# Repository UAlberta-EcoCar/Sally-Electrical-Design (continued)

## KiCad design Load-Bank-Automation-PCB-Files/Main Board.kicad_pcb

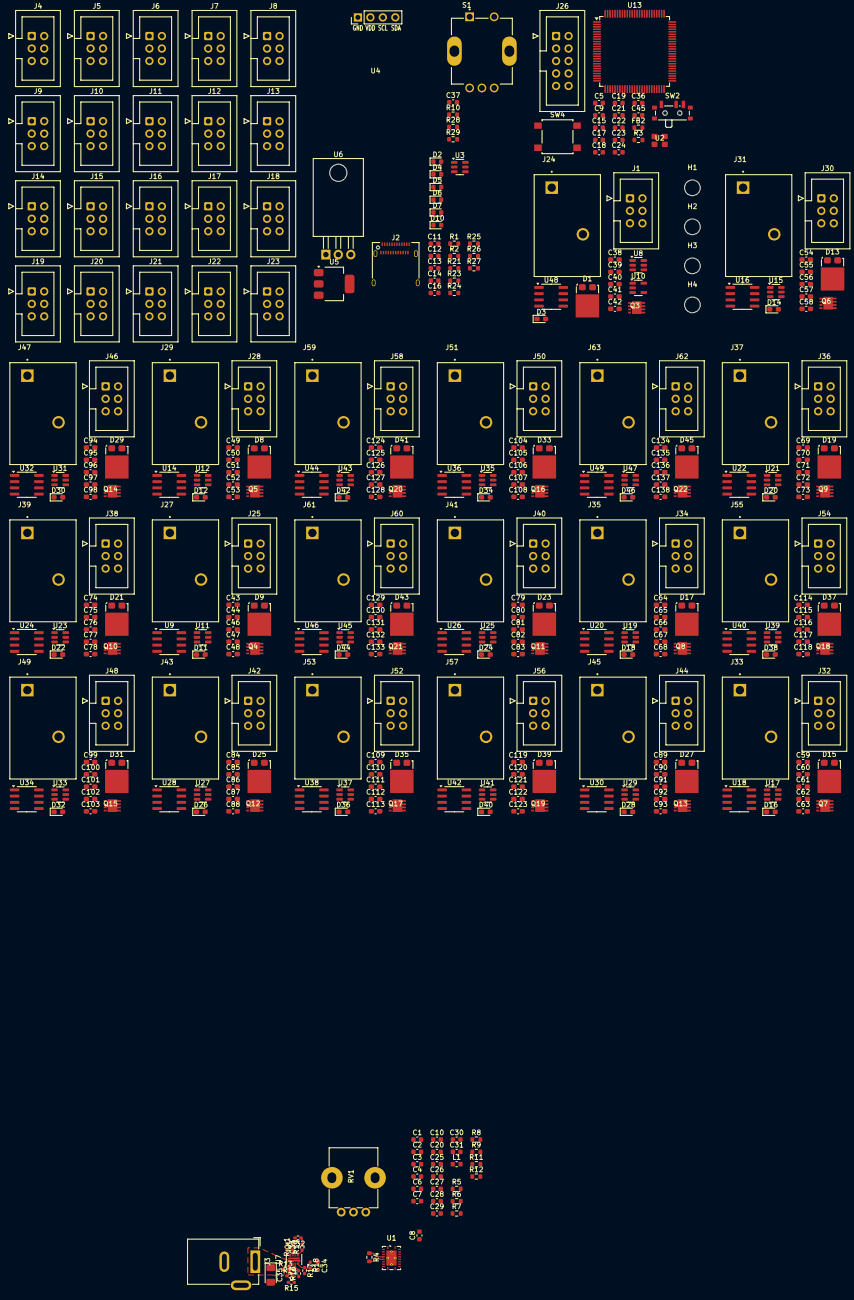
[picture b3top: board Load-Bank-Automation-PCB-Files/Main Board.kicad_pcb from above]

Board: 2 copper layers, 354 parts (0 on the bottom side), 237 nets.

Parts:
C1: 2200n; C_0603_1608Metric
C2: 82p; C_0603_1608Metric
C3, C5, C9, C12, C13, C14, C17, C18, C19, C21, C31, C36, C37, C45: 100n; C_0603_1608Metric
C4: 47n; C_0603_1608Metric
C6, C16, C20, C25, C26: 10u; C_0603_1608Metric
C7, C27, C28, C29: 22u; C_0603_1608Metric
C8: 5.6n; C_0603_1608Metric
C10: 820p; C_0603_1608Metric
C11: 330n; C_0603_1608Metric
C15: 4u7; C_0603_1608Metric
C22: 10n; C_0603_1608Metric
C23, C24: 1u; C_0603_1608Metric
C30: 12p; C_0603_1608Metric
C32: 2200p; R_0402_1005Metric_Pad0.72x0.64mm_HandSolder
C33: C; R_0402_1005Metric_Pad0.72x0.64mm_HandSolder
C34: 240u; R_0603_1608Metric
C35: 100u; D_1206_3216Metric_Pad1.42x1.75mm_HandSolder
C38, C39, C43, C44, C49, C50, C54, C55, C59, C60, C64, C65, C69, C70, C74, C75, C79, C80, C84, C85, C89, C90, C94, C95, C99, C100, C104, C105, C109, C110, C114, C115, C119, C120, C124, C125, C129, C130, C134, C135: 100u; C_0603_1608Metric_Pad1.08x0.95mm_HandSolder
C40, C41, C46, C47, C51, C52, C56, C57, C61, C62, C66, C67, C71, C72, C76, C77, C81, C82, C86, C87, C91, C92, C96, C97, C101, C102, C106, C107, C111, C112, C116, C117, C121, C122, C126, C127, C131, C132, C136, C137: C; C_0603_1608Metric_Pad1.08x0.95mm_HandSolder
C42, C48, C53, C58, C63, C68, C73, C78, C83, C88, C93, C98, C103, C108, C113, C118, C123, C128, C133, C138: 0.1u; C_0603_1608Metric_Pad1.08x0.95mm_HandSolder
D1, D8, D9, D13, D15, D17, D19, D21, D23, D25, D27, D29, D31, D33, D35, D37, D39, D41, D43, D45: STPS5H100SFY; TO-277A
D2, D4, D5, D6, D7, D10: LED; LED_0603_1608Metric
D3, D11, D12, D14, D16, D18, D20, D22, D24, D26, D28, D30, D32, D34, D36, D38, D40, D42, D44, D46: LED; LED_0603_1608Metric_Pad1.05x0.95mm_HandSolder
FB2: 300R; R_0603_1608Metric
H1, H2, H3, H4: MountingHole; MountingHole_3.2mm_M3
J1, J4, J5, J6, J7, J8, J9, J10, J11, J12, J13, J14, J15, J16, J17, J18, J19, J20, J21, J22, J23, J25, J28, J30, J32, J34, J36, J38, J40, J42, J44, J46, J48, J50, J52, J54, J56, J58, J60, J62: Conn_02x03_Counter_Clockwise; IDC-Header_2x03_P2.54mm_Vertical
J2: USB_C_Receptacle_USB2.0_14P; USB_C_Receptacle_Amphenol_12401610E4-2A
J3: Barrel_Jack_MountingPin; BarrelJack_GCT_DCJ200-10-A_Horizontal
J24, J27, J29, J31, J33, J35, J37, J39, J41, J43, J45, J47, J49, J51, J53, J55, J57, J59, J61, J63: PHNX_CONN_1017521; PHOENIX_1017521
J26: STM32-Prog-Header; IDC-STM32-Prog-Header_2x05_P2.54mm_Vertical
L1: 5600n; L_0603_1608Metric
Q3, Q4, Q5, Q6, Q7, Q8, Q9, Q10, Q11, Q12, Q13, Q14, Q15, Q16, Q17, Q18, Q19, Q20, Q21, Q22: GSGN0648; Goodarksemiconductor_PPAK_3x3
R1, R2: 5k1; R_0603_1608Metric
R3: 10K; R_0603_1608Metric
R4: 1.5k; R_0603_1608Metric
R5: 10k; R_0603_1608Metric
R6: 500; R_0603_1608Metric
R7: 21k; R_0603_1608Metric
R8: 23.7k; R_0603_1608Metric
R9: 100; R_0603_1608Metric
R10: 5K; R_0603_1608Metric
R11: 80k6; R_0603_1608Metric
R12, R23, R24, R27: 7k5; R_0603_1608Metric
R13: 470k; R_0402_1005Metric_Pad0.72x0.64mm_HandSolder
R14: 16k; R_0402_1005Metric_Pad0.72x0.64mm_HandSolder
R15: 25k; R_0402_1005Metric_Pad0.72x0.64mm_HandSolder
R16, R18: 47K; R_0402_1005Metric_Pad0.72x0.64mm_HandSolder
R17: 3k9; R_0402_1005Metric_Pad0.72x0.64mm_HandSolder
R19: 100; R_0402_1005Metric_Pad0.72x0.64mm_HandSolder
R21: 2k; R_0603_1608Metric
R25, R26: 600; R_0603_1608Metric
R28, R29: 4k7; R_0603_1608Metric
RV1: 10K; Potentiometer_Bourns_PTV09A-4_Single_Vertical
R_{ILM}1: 750; R_0402_1005Metric_Pad0.72x0.64mm_HandSolder
S1: PEC12R-4220F-S0024; XDCR_PEC12R-4220F-S0024
SW2: SW_SPDT; SW_SPDT_PCM12
SW4: RESET; SW_SPST_B3S-1000
U1: LM25145RGYT; Texas_RGY_R-PVQFN-N20_EP2.05x3.05mm_ThermalVias
U2: OXETDLJANF-8MHz
U3: USBLC6-2SC6; SOT-23-6
U4: 1306 OLED Display; Display_128x64_096_I2C
U5: LD1117S33TR_SOT223; SOT-223-3_TabPin2
U6: L7805; TO-220-3_Horizontal_TabDown
U7: TPS259474LRPWR; RPW0010A-MFG
U8, U11, U12, U15, U17, U19, U21, U23, U25, U27, U29, U31, U33, U35, U37, U39, U41, U43, U45, U47: IRS10752LPBF; SOT-23-6
U9, U14, U16, U18, U20, U22, U24, U26, U28, U30, U32, U34, U36, U38, U40, U42, U44, U46, U48, U49: ACS711xLCTR-25AB; SOIC-8_3.9x4.9mm_P1.27mm
U10: MCP6006-OTVAO; SOT-23-5
U13: STM32G491VETx; LQFP-100_14x14mm_P0.5mm

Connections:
+3V3: C5.1, C9.1, C15.1, C16.1, C17.1, C18.1, C19.1, C21.1, C24.1, C36.1, C42.2, C48.2, C53.2, C58.2, C63.2, C68.2, C73.2, C78.2, C83.2, C88.2, C93.2, C98.2, C103.2, C108.2, C113.2, C118.2, C123.2, C128.2, C133.2, C138.2, FB2.2, J1.1, J4.1, J5.1, J6.1, J7.1, J8.1, J9.1, J10.1, J11.1, J12.1, J13.1, J14.1, J15.1, J16.1, J17.1, J18.1, J19.1, J20.1, J21.1, J22.1, J23.1, J25.1, J26.7 (3.3V), J26.8 (3.3V), J28.1, J30.1, J32.1, J34.1, J36.1, J38.1, J40.1, J42.1, J44.1, J46.1, J48.1, J50.1, J52.1, J54.1, J56.1, J58.1, J60.1, J62.1, R24.1, R28.1, R29.1, SW2.1 (A), U2.1 (Tri-State), U2.4 (VDD), U5.2 (VO), U9.8 (VCC), U10.5 (V+), U13.6 (VBAT), U13.24 (VDD), U13.36 (VREF+), U13.49 (VDD), U13.64 (VDD), U13.75 (VDD), U13.100 (VDD), U14.8 (VCC), U16.8 (VCC), U18.8 (VCC), U20.8 (VCC), U22.8 (VCC), U24.8 (VCC), U26.8 (VCC), U28.8 (VCC), U30.8 (VCC), U32.8 (VCC), U34.8 (VCC), U36.8 (VCC), U38.8 (VCC), U40.8 (VCC), U42.8 (VCC), U44.8 (VCC), U46.8 (VCC), U48.8 (VCC), U49.8 (VCC)
+3VA3: C22.1, C23.1, FB2.1, U13.37 (VDDA)
+5V: C12.1, C13.1, C14.1, J26.9 (5V), J26.10 (5V), R10.1, R23.1, U3.5 (VBUS), U5.3 (VI), U6.3 (OUT)
+12V: C7.1, C11.1, C27.1, C28.1, C29.1, C38.2, C43.2, C49.2, C54.2, C59.2, C64.2, C69.2, C74.2, C79.2, C84.2, C89.2, C94.2, C99.2, C104.2, C109.2, C114.2, C119.2, C124.2, C129.2, C134.2, D1.2 (A), D8.2 (A), D9.2 (A), D13.2 (A), D15.2 (A), D17.2 (A), D19.2 (A), D21.2 (A), D23.2 (A), D25.2 (A), D27.2 (A), D29.2 (A), D31.2 (A), D33.2 (A), D35.2 (A), D37.2 (A), D39.2 (A), D41.2 (A), D43.2 (A), D45.2 (A), J1.6, J4.6, J5.6, J6.6, J7.6, J8.6, J9.6, J10.6, J11.6, J12.6, J13.6, J14.6, J15.6, J16.6, J17.6, J18.6, J19.6, J20.6, J21.6, J22.6, J23.6, J25.6, J28.6, J30.6, J32.6, J34.6, J36.6, J38.6, J40.6, J42.6, J44.6, J46.6, J48.6, J50.6, J52.6, J54.6, J56.6, J58.6, J60.6, J62.6, L1.2, R7.1, R9.1, R27.1, U6.1 (IN), U8.1 (V_{cc}), U11.1 (V_{cc}), U12.1 (V_{cc}), U15.1 (V_{cc}), U17.1 (V_{cc}), U19.1 (V_{cc}), U21.1 (V_{cc}), U23.1 (V_{cc}), U25.1 (V_{cc}), U27.1 (V_{cc}), U29.1 (V_{cc}), U31.1 (V_{cc}), U33.1 (V_{cc}), U35.1 (V_{cc}), U37.1 (V_{cc}), U39.1 (V_{cc}), U41.1 (V_{cc}), U43.1 (V_{cc}), U45.1 (V_{cc}), U47.1 (V_{cc})
/MCU_USB/BOOT0: R3.1, U13.95 (PB8)
/MCU_USB/RCC_OSC_IN: U2.3 (OUT), U13.12 (PF0)
/MCU_USB/SWCLK: J26.2 (SWCLK), U13.77 (PA14)
/MCU_USB/SWDIO: J26.4 (SWDIO), U13.76 (PA13)
/MOSFET Boards/First Mosfet Board 1/Current_ADC: C41.2, J1.2, U48.7 (VIOUT)
/MOSFET Boards/First Mosfet Board 1/PWM: J1.5, U8.3 (IN)
/MOSFET Boards/First Mosfet Board 1/V_{IN}: J24.1, U48.1 (IP+), U48.2 (IP+)
/MOSFET Boards/First Mosfet Board 1/V_{OUT}: J24.2, Q3.1 (S), Q3.2 (S), Q3.3 (S)
/MOSFET Boards/First Mosfet Board 1/Voltage_ADC: J1.4, U10.1, U10.4 (-)
/MOSFET Boards/MOSFET Board 2/Current_ADC: C47.2, J25.2, U9.7 (VIOUT)
/MOSFET Boards/MOSFET Board 2/PWM: J25.5, U11.3 (IN)
/MOSFET Boards/MOSFET Board 2/V_{IN}: J27.1, U9.1 (IP+), U9.2 (IP+)
/MOSFET Boards/MOSFET Board 2/V_{OUT}: J27.2, Q4.1 (S), Q4.2 (S), Q4.3 (S)
/MOSFET Boards/MOSFET Board 3/Current_ADC: C52.2, J28.2, U14.7 (VIOUT)
/MOSFET Boards/MOSFET Board 3/PWM: J28.5, U12.3 (IN)
/MOSFET Boards/MOSFET Board 3/V_{IN}: J29.1, U14.1 (IP+), U14.2 (IP+)
/MOSFET Boards/MOSFET Board 3/V_{OUT}: J29.2, Q5.1 (S), Q5.2 (S), Q5.3 (S)
/MOSFET Boards/MOSFET Board 4/Current_ADC: C57.2, J30.2, U16.7 (VIOUT)
/MOSFET Boards/MOSFET Board 4/PWM: J30.5, U15.3 (IN)
/MOSFET Boards/MOSFET Board 4/V_{IN}: J31.1, U16.1 (IP+), U16.2 (IP+)
/MOSFET Boards/MOSFET Board 4/V_{OUT}: J31.2, Q6.1 (S), Q6.2 (S), Q6.3 (S)
/MOSFET Boards/MOSFET Board 5/Current_ADC: C62.2, J32.2, U18.7 (VIOUT)
/MOSFET Boards/MOSFET Board 5/PWM: J32.5, U17.3 (IN)
/MOSFET Boards/MOSFET Board 5/V_{IN}: J33.1, U18.1 (IP+), U18.2 (IP+)
/MOSFET Boards/MOSFET Board 5/V_{OUT}: J33.2, Q7.1 (S), Q7.2 (S), Q7.3 (S)
/MOSFET Boards/MOSFET Board 6/Current_ADC: C67.2, J34.2, U20.7 (VIOUT)
/MOSFET Boards/MOSFET Board 6/PWM: J34.5, U19.3 (IN)
/MOSFET Boards/MOSFET Board 6/V_{IN}: J35.1, U20.1 (IP+), U20.2 (IP+)
/MOSFET Boards/MOSFET Board 6/V_{OUT}: J35.2, Q8.1 (S), Q8.2 (S), Q8.3 (S)
/MOSFET Boards/MOSFET Board 7/Current_ADC: C72.2, J36.2, U22.7 (VIOUT)
/MOSFET Boards/MOSFET Board 7/PWM: J36.5, U21.3 (IN)
/MOSFET Boards/MOSFET Board 7/V_{IN}: J37.1, U22.1 (IP+), U22.2 (IP+)
/MOSFET Boards/MOSFET Board 7/V_{OUT}: J37.2, Q9.1 (S), Q9.2 (S), Q9.3 (S)
/MOSFET Boards/MOSFET Board 8/Current_ADC: C77.2, J38.2, U24.7 (VIOUT)
/MOSFET Boards/MOSFET Board 8/PWM: J38.5, U23.3 (IN)
/MOSFET Boards/MOSFET Board 8/V_{IN}: J39.1, U24.1 (IP+), U24.2 (IP+)
/MOSFET Boards/MOSFET Board 8/V_{OUT}: J39.2, Q10.1 (S), Q10.2 (S), Q10.3 (S)
/MOSFET Boards/MOSFET Board 9/Current_ADC: C82.2, J40.2, U26.7 (VIOUT)
/MOSFET Boards/MOSFET Board 9/PWM: J40.5, U25.3 (IN)
/MOSFET Boards/MOSFET Board 9/V_{IN}: J41.1, U26.1 (IP+), U26.2 (IP+)
/MOSFET Boards/MOSFET Board 9/V_{OUT}: J41.2, Q11.1 (S), Q11.2 (S), Q11.3 (S)
/MOSFET Boards/MOSFET Board 10/Current_ADC: C87.2, J42.2, U28.7 (VIOUT)
/MOSFET Boards/MOSFET Board 10/PWM: J42.5, U27.3 (IN)
/MOSFET Boards/MOSFET Board 10/V_{IN}: J43.1, U28.1 (IP+), U28.2 (IP+)
/MOSFET Boards/MOSFET Board 10/V_{OUT}: J43.2, Q12.1 (S), Q12.2 (S), Q12.3 (S)
/MOSFET Boards/MOSFET Board 11/Current_ADC: C92.2, J44.2, U30.7 (VIOUT)
/MOSFET Boards/MOSFET Board 11/PWM: J44.5, U29.3 (IN)
/MOSFET Boards/MOSFET Board 11/V_{IN}: J45.1, U30.1 (IP+), U30.2 (IP+)
/MOSFET Boards/MOSFET Board 11/V_{OUT}: J45.2, Q13.1 (S), Q13.2 (S), Q13.3 (S)
/MOSFET Boards/MOSFET Board 12/Current_ADC: C97.2, J46.2, U32.7 (VIOUT)
/MOSFET Boards/MOSFET Board 12/PWM: J46.5, U31.3 (IN)
/MOSFET Boards/MOSFET Board 12/V_{IN}: J47.1, U32.1 (IP+), U32.2 (IP+)
/MOSFET Boards/MOSFET Board 12/V_{OUT}: J47.2, Q14.1 (S), Q14.2 (S), Q14.3 (S)
/MOSFET Boards/MOSFET Board 13/Current_ADC: C102.2, J48.2, U34.7 (VIOUT)
/MOSFET Boards/MOSFET Board 13/PWM: J48.5, U33.3 (IN)
/MOSFET Boards/MOSFET Board 13/V_{IN}: J49.1, U34.1 (IP+), U34.2 (IP+)
/MOSFET Boards/MOSFET Board 13/V_{OUT}: J49.2, Q15.1 (S), Q15.2 (S), Q15.3 (S)
/MOSFET Boards/MOSFET Board 14/Current_ADC: C107.2, J50.2, U36.7 (VIOUT)
/MOSFET Boards/MOSFET Board 14/PWM: J50.5, U35.3 (IN)
/MOSFET Boards/MOSFET Board 14/V_{IN}: J51.1, U36.1 (IP+), U36.2 (IP+)
/MOSFET Boards/MOSFET Board 14/V_{OUT}: J51.2, Q16.1 (S), Q16.2 (S), Q16.3 (S)
/MOSFET Boards/MOSFET Board 15/Current_ADC: C112.2, J52.2, U38.7 (VIOUT)
/MOSFET Boards/MOSFET Board 15/PWM: J52.5, U37.3 (IN)
/MOSFET Boards/MOSFET Board 15/V_{IN}: J53.1, U38.1 (IP+), U38.2 (IP+)
/MOSFET Boards/MOSFET Board 15/V_{OUT}: J53.2, Q17.1 (S), Q17.2 (S), Q17.3 (S)
/MOSFET Boards/MOSFET Board 16/Current_ADC: C117.2, J54.2, U40.7 (VIOUT)
/MOSFET Boards/MOSFET Board 16/PWM: J54.5, U39.3 (IN)
/MOSFET Boards/MOSFET Board 16/V_{IN}: J55.1, U40.1 (IP+), U40.2 (IP+)
/MOSFET Boards/MOSFET Board 16/V_{OUT}: J55.2, Q18.1 (S), Q18.2 (S), Q18.3 (S)
/MOSFET Boards/MOSFET Board 17/Current_ADC: C122.2, J56.2, U42.7 (VIOUT)
/MOSFET Boards/MOSFET Board 17/PWM: J56.5, U41.3 (IN)
/MOSFET Boards/MOSFET Board 17/V_{IN}: J57.1, U42.1 (IP+), U42.2 (IP+)
/MOSFET Boards/MOSFET Board 17/V_{OUT}: J57.2, Q19.1 (S), Q19.2 (S), Q19.3 (S)
/MOSFET Boards/MOSFET Board 18/Current_ADC: C127.2, J58.2, U44.7 (VIOUT)
/MOSFET Boards/MOSFET Board 18/PWM: J58.5, U43.3 (IN)
/MOSFET Boards/MOSFET Board 18/V_{IN}: J59.1, U44.1 (IP+), U44.2 (IP+)
/MOSFET Boards/MOSFET Board 18/V_{OUT}: J59.2, Q20.1 (S), Q20.2 (S), Q20.3 (S)
/MOSFET Boards/MOSFET Board 19/Current_ADC: C132.2, J60.2, U46.7 (VIOUT)
/MOSFET Boards/MOSFET Board 19/PWM: J60.5, U45.3 (IN)
/MOSFET Boards/MOSFET Board 19/V_{IN}: J61.1, U46.1 (IP+), U46.2 (IP+)
/MOSFET Boards/MOSFET Board 19/V_{OUT}: J61.2, Q21.1 (S), Q21.2 (S), Q21.3 (S)
/MOSFET Boards/MOSFET Board 20/Current_ADC: C137.2, J62.2, U49.7 (VIOUT)
/MOSFET Boards/MOSFET Board 20/PWM: J62.5, U47.3 (IN)
/MOSFET Boards/MOSFET Board 20/V_{IN}: J63.1, U49.1 (IP+), U49.2 (IP+)
/MOSFET Boards/MOSFET Board 20/V_{OUT}: J63.2, Q22.1 (S), Q22.2 (S), Q22.3 (S)
/Main_Power/DC-DC Buck/Protected_18V: C6.1, C20.1, C25.1, C26.1, C31.1, C34.1, R11.2, R18.1, U1.20 (VIN), U7.6 (OUT)
/Main_Power/eFuse/Unprotected_18V: C35.1, J3.1, R13.1, U7.5 (IN)
ADC1_IN1: J5.2, U13.20 (PA0)
ADC1_IN2: J6.2, U13.21 (PA1)
ADC1_IN3: J7.2, U13.22 (PA2)
ADC1_IN4: J8.2, U13.25 (PA3)
ADC1_IN5: J17.2, U13.53 (PB14)
ADC1_IN6: J19.2, U13.15 (PC0)
ADC1_IN7: J20.2, U13.16 (PC1)
ADC1_IN8: J21.2, U13.17 (PC2)
ADC1_IN11: J16.2, U13.51 (PB12)
ADC1_IN12: J13.2, U13.33 (PB1)
ADC1_IN14: J15.2, U13.50 (PB11)
ADC1_IN15: J12.2, U13.32 (PB0)
ADC2_IN3: J10.2, U13.28 (PA6)
ADC2_IN4: J11.2, U13.29 (PA7)
ADC2_IN9: J22.2, U13.18 (PC3)
ADC2_IN10: J4.2, U13.13 (PF1)
ADC2_IN11: J23.2, U13.31 (PC5)
ADC2_IN12: J14.2, U13.34 (PB2)
ADC2_IN15: J18.2, U13.54 (PB15)
ADC2_IN17: J9.2, U13.26 (PA4)
ADC3_IN3: J4.4, U13.44 (PE13)
Encoder CLK A: S1.A (CHANNEL_A), U13.97 (PE0)
Encoder CLK B: S1.B (CHANNEL_B), U13.81 (PC12)
Encoder Push SW: C37.1, S1.2, U13.98 (PE1)
GND: C1.2, C4.1, C22.2, C23.2, C24.2, C30.1, C32.2, C33.1, C34.2, C35.2, C37.2, C38.1, C41.1, C42.1, C43.1, C45.1, C47.1, C48.1, C49.1, C52.1, C53.1, C54.1, C57.1, C58.1, C59.1, C62.1, C63.1, C64.1, C67.1, C68.1, C69.1, C72.1, C73.1, C74.1, C77.1, C78.1, C79.1, C82.1, C83.1, C84.1, C87.1, C88.1, C89.1, C92.1, C93.1, C94.1, C97.1, C98.1, C99.1, C102.1, C103.1, C104.1, C107.1, C108.1, C109.1, C112.1, C113.1, C114.1, C117.1, C118.1, C119.1, C122.1, C123.1, C124.1, C127.1, C128.1, C129.1, C132.1, C133.1, C134.1, C137.1, C138.1, D3.1 (K), D11.1 (K), D12.1 (K), D14.1 (K), D16.1 (K), D18.1 (K), D20.1 (K), D22.1 (K), D24.1 (K), D26.1 (K), D28.1 (K), D30.1 (K), D32.1 (K), D34.1 (K), D36.1 (K), D38.1 (K), D40.1 (K), D42.1 (K), D44.1 (K), D46.1 (K), J1.3, J4.3, J5.3, J6.3, J7.3, J8.3, J9.3, J10.3, J11.3, J12.3, J13.3, J14.3, J15.3, J16.3, J17.3, J18.3, J19.3, J20.3, J21.3, J22.3, J23.3, J25.3, J28.3, J30.3, J32.3, J34.3, J36.3, J38.3, J40.3, J42.3, J44.3, J46.3, J48.3, J50.3, J52.3, J54.3, J56.3, J58.3, J60.3, J62.3, R4.2, R8.2, R15.2, R17.2, RV1.3, RV1.MP (MountPin), R_{ILM}1.2, SW4.1, U1.6 (AGND), U1.8 (SYNCIN), U7.8 (GND), U8.2 (COM), U9.5 (GND), U10.2 (V-), U11.2 (COM), U12.2 (COM), U14.5 (GND), U15.2 (COM), U16.5 (GND), U17.2 (COM), U18.5 (GND), U19.2 (COM), U20.5 (GND), U21.2 (COM), U22.5 (GND), U23.2 (COM), U24.5 (GND), U25.2 (COM), U26.5 (GND), U27.2 (COM), U28.5 (GND), U29.2 (COM), U30.5 (GND), U31.2 (COM), U32.5 (GND), U33.2 (COM), U34.5 (GND), U35.2 (COM), U36.5 (GND), U37.2 (COM), U38.5 (GND), U39.2 (COM), U40.5 (GND), U41.2 (COM), U42.5 (GND), U43.2 (COM), U44.5 (GND), U45.2 (COM), U46.5 (GND), U47.2 (COM), U48.5 (GND), U49.5 (GND)
GNDREF: C5.2, C6.2, C7.2, C9.2, C11.2, C12.2, C13.2, C14.2, C15.2, C16.2, C17.2, C18.2, C19.2, C20.2, C21.2, C25.2, C26.2, C27.2, C28.2, C29.2, C31.2, C36.2, D2.1 (K), D4.1 (K), D5.1 (K), D6.1 (K), D7.1 (K), D10.1 (K), J2.S1 (SHIELD), J3.2, J26.5 (GND), J26.6 (GND), R1.1, R2.1, R12.1, S1.C (COMMON), SW2.3 (C), U1.12 (PGND), U2.2 (GND), U3.2 (GND), U5.1 (GND), U6.2 (GND), U13.23 (VSS), U13.35 (VSSA), U13.48 (VSS), U13.63 (VSS), U13.74 (VSS), U13.99 (VSS)
LED_1: R25.1, U13.83 (PD1)
LED_2: R26.1, U13.7 (PC13)
unnamed: C8.1, R5.2
unnamed: C10.1, R9.2
unnamed: C32.1, R19.2
unnamed: C39.2, D1.1 (K), U8.4 (V_{B})
unnamed: D2.2 (A), R23.2
unnamed: D4.2 (A), R24.2
unnamed: D5.2 (A), R25.2
unnamed: D6.2 (A), R26.2
unnamed: D7.2 (A), R27.2
unnamed: C50.2, D8.1 (K), U12.4 (V_{B})
unnamed: C44.2, D9.1 (K), U11.4 (V_{B})
unnamed: D10.2 (A), R21.2
unnamed: C55.2, D13.1 (K), U15.4 (V_{B})
unnamed: C60.2, D15.1 (K), U17.4 (V_{B})
unnamed: C65.2, D17.1 (K), U19.4 (V_{B})
unnamed: C70.2, D19.1 (K), U21.4 (V_{B})
unnamed: C75.2, D21.1 (K), U23.4 (V_{B})
unnamed: C80.2, D23.1 (K), U25.4 (V_{B})
unnamed: C85.2, D25.1 (K), U27.4 (V_{B})
unnamed: C90.2, D27.1 (K), U29.4 (V_{B})
unnamed: C95.2, D29.1 (K), U31.4 (V_{B})
unnamed: C100.2, D31.1 (K), U33.4 (V_{B})
unnamed: C105.2, D33.1 (K), U35.4 (V_{B})
unnamed: C110.2, D35.1 (K), U37.4 (V_{B})
unnamed: C115.2, D37.1 (K), U39.4 (V_{B})
unnamed: C120.2, D39.1 (K), U41.4 (V_{B})
unnamed: C125.2, D41.1 (K), U43.4 (V_{B})
unnamed: C130.2, D43.1 (K), U45.4 (V_{B})
unnamed: C135.2, D45.1 (K), U47.4 (V_{B})
unnamed: J2.A5 (CC1), R1.2
unnamed: J2.B5 (CC2), R2.2
unnamed: J2.A6 (D+), J2.B6 (D+), U3.3 (I/O2)
unnamed: J2.A7 (D-), J2.B7 (D-), U3.1 (I/O1)
unnamed: C40.1, U48.3 (IP-), U48.4 (IP-)
unnamed: C46.1, U9.3 (IP-), U9.4 (IP-)
unnamed: C51.1, U14.3 (IP-), U14.4 (IP-)
unnamed: C56.1, U16.3 (IP-), U16.4 (IP-)
unnamed: C61.1, U18.3 (IP-), U18.4 (IP-)
unnamed: C66.1, U20.3 (IP-), U20.4 (IP-)
unnamed: C71.1, U22.3 (IP-), U22.4 (IP-)
unnamed: C76.1, U24.3 (IP-), U24.4 (IP-)
unnamed: C81.1, U26.3 (IP-), U26.4 (IP-)
unnamed: C86.1, U28.3 (IP-), U28.4 (IP-)
unnamed: C91.1, U30.3 (IP-), U30.4 (IP-)
unnamed: C96.1, U32.3 (IP-), U32.4 (IP-)
unnamed: C101.1, U34.3 (IP-), U34.4 (IP-)
unnamed: C106.1, U36.3 (IP-), U36.4 (IP-)
unnamed: C111.1, U38.3 (IP-), U38.4 (IP-)
unnamed: C116.1, U40.3 (IP-), U40.4 (IP-)
unnamed: C121.1, U42.3 (IP-), U42.4 (IP-)
unnamed: C126.1, U44.3 (IP-), U44.4 (IP-)
unnamed: C131.1, U46.3 (IP-), U46.4 (IP-)
unnamed: C136.1, U49.3 (IP-), U49.4 (IP-)
unnamed: R7.2, RV1.1
unnamed: R10.2, S1.1
unnamed: R3.2, SW2.2 (B)
unnamed: C3.1, U1.17 (BST)
unnamed: C2.2, C8.2, U1.4 (COMP)
unnamed: R11.1, R12.2, U1.1 (EN_UVLO)
unnamed: C2.1, C10.2, R4.1, R5.1, RV1.2, U1.5 (FB)
unnamed: C30.2, R6.1, U1.11 (ILIM)
unnamed: R8.1, U1.2 (RT)
unnamed: C4.2, U1.3 (SS_TRK)
unnamed: C3.2, L1.1, U1.19 (SW)
unnamed: C1.1, U1.14 (VCC)
unnamed: R19.1, U7.7 (DVDT)
unnamed: R13.2, R14.1, U7.1 (EN/UVLO)
unnamed: R_{ILM}1.1, U7.9 (ILM)
unnamed: C33.2, U7.10 (ITIMER)
unnamed: R14.2, R15.1, U7.2 (OVLO)
unnamed: R16.2, U7.3 (PG)
unnamed: R17.1, R18.2, U7.4 (PGTH)
unnamed: C39.1, U8.6 (V_{s})
unnamed: C44.1, U11.6 (V_{s})
unnamed: C50.1, U12.6 (V_{s})
unnamed: C45.2, SW4.2, U13.14 (PG10)
unnamed: C55.1, U15.6 (V_{s})
unnamed: C60.1, U17.6 (V_{s})
unnamed: C65.1, U19.6 (V_{s})
unnamed: C70.1, U21.6 (V_{s})
unnamed: C75.1, U23.6 (V_{s})
unnamed: C80.1, U25.6 (V_{s})
unnamed: C85.1, U27.6 (V_{s})
unnamed: C90.1, U29.6 (V_{s})
unnamed: C95.1, U31.6 (V_{s})
unnamed: C100.1, U33.6 (V_{s})
unnamed: C105.1, U35.6 (V_{s})
unnamed: C110.1, U37.6 (V_{s})
unnamed: C115.1, U39.6 (V_{s})
unnamed: C120.1, U41.6 (V_{s})
unnamed: C125.1, U43.6 (V_{s})
unnamed: C130.1, U45.6 (V_{s})
unnamed: C135.1, U47.6 (V_{s})
OLED SCL: R28.2, U13.30 (PC4)
OLED SDA: R29.2, U13.69 (PA8)
TIM1_CH1: J8.5, U13.40 (PE9)
TIM1_CH2: J9.5, U13.42 (PE11)
TIM2_CH1: J15.5, U13.27 (PA5)
TIM2_CH2: J10.5, U13.86 (PD4)
TIM2_CH3: J19.5, U13.47 (PB10)
TIM2_CH4: J16.5, U13.71 (PA10)
TIM3_CH1: J17.5, U13.91 (PB4)
TIM3_CH2: J18.5, U13.92 (PB5)
TIM3_CH3: J6.5, U13.3 (PE4)
TIM3_CH4: J7.5, U13.4 (PE5)
TIM4_CH1: J11.5, U13.59 (PD12)
TIM4_CH2: J12.5, U13.60 (PD13)
TIM4_CH3: J13.5, U13.61 (PD14)
TIM4_CH4: J14.5, U13.62 (PD15)
TIM8_CH1: J20.5, U13.65 (PC6)
TIM8_CH2: J21.5, U13.66 (PC7)
TIM8_CH3: J22.5, U13.67 (PC8)
TIM8_CH4: J23.5, U13.68 (PC9)
TIM15_CH1: J4.5, U13.10 (PF9)
TIM15_CH2: J5.5, U13.11 (PF10)
USB_D+: U3.4 (I/O2), U13.73 (PA12)
USB_D-: U3.6 (I/O1), U13.72 (PA11)
VBUS: J2.A4 (VBUS), J2.A9 (VBUS), J2.B4 (VBUS), J2.B9 (VBUS), R21.1
